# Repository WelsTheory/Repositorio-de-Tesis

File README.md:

# Diseño e implementación de un sistema de adquisición digital programable para señales ECG
Repositorio de la tesis "Diseño e implementación de un sistema de adquisición digital programable para señales ECG". Autor: William's Limonchi Sandoval
## Requisitos
Es necesario tener instalado los siguientes programas:
* [Matlab](https://www.mathworks.com/products/matlab.html) - La versión 2014 o superior
* [XC16](https://www.microchip.com/mplab/compilers) - El compilador XC16 para generar el programa del microcontrolador
* [Device Blocks for Simulink](https://www.microchip.com/forums/m878432.aspx) - Herramienta para trabajar con Microchip en Simulink
También es necesario tener la tarjeta de adquisición de la investigación para poder trabajar con el sistema. Los archivos de la tarjeta se encuentran en la carpeta Demo SAQD_ECG/Diseño Hardware_KiCad
### Carpetas del repositorio
* Carpeta de pruebas:
En esta carpeta se encuentran todos los ejemplos realizados antes de obtener el trabajo final
* Demo SAQD_ECG:
En esta carpeta se encuentra el programa principal de la tesis, desde el diseño de hardware de la investigación hasta el programa final con su interfaz gráfica.
* Ejemplos:
En esta carpeta se encuentran diferentes ejemplos que se han unido con el sistema. 
1) Downsamplin, para obtener otro tiempo de muestreos.
2) Filtros butterworth, para saber como trabajan los filtros butterworth con la investigación.
3) Filtros de 1er orden, son filtros sencillos de 1er orden para saber como trabaja la investigación
4) Sistema con tres filtros, es el programa principal con sólo 3 filtros.
5) Sistema con un único filtro, es el programa principal con un único filtro.
Estos programas son ejemplos para modificar el bloque Programable del programa principal. 
* Framework:
En esta carpeta se encuentra una copia del programa principal de la investigación, esto para poder modificar este programa sin necesidad de causar un error en el demo de la investigación.
## Contribución
Para contribuir con la investigación primero se debe hacer un fork al repositorio y seguidamente se puede enviar los cambios o modificaciones al correo: williams.limonchi.sandoval@gmail.com
## Version 
Esta investigación está en la versión 1.0.1 por lo que aún hay detalles que pulir y mejorar.
## Autor
William's Limonchi Sandoval [Twitter](http://twitter.com/welstheory)

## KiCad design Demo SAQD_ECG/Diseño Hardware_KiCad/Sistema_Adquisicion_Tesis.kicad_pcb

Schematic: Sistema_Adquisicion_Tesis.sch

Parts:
C1, C9: 100nF; C_Disc_D4.3mm_W1.9mm_P5.00mm
C2: 220uF; CP_Radial_D10.0mm_P5.00mm
C3, C4: 15pF; C_Disc_D3.0mm_W1.6mm_P2.50mm
C5, C6, C7, C8: 10uF; CP_Radial_D6.3mm_P2.50mm
D1, D2: 1N4148; D_DO-35_SOD27_P7.62mm_Horizontal
D3, D4: LED; LED_D5.0mm
J1: Barrel_Jack_Switch; Jack_Horizontal
J2: USB_SERIAL; PinHeader_1x04_P2.54mm_Vertical
J3: Signal_INA; PinHeader_1x03_P2.54mm_Vertical
J4: Offset; PinHeader_1x03_P2.54mm_Vertical
J5: Electrodos; Jack_3.5mm_Ledino_KB3SPRS_Horizontal
J6: DAC; PinHeader_1x03_P2.54mm_Vertical
J7: GND; PinHeader_1x02_P2.54mm_Vertical
J8: PORTA; PinSocket_1x05_P2.54mm_Vertical
J9: S_Fuente; PinHeader_1x03_P2.54mm_Vertical
J10: Pickit; PinHeader_1x05_P2.54mm_Vertical
J11: 3.3v; PinHeader_1x02_P2.54mm_Vertical
J12: PORTB; PinSocket_1x09_P2.54mm_Vertical
J13: V+; PinHeader_1x02_P2.54mm_Vertical
J14: V-; PinHeader_1x02_P2.54mm_Vertical
Q1: 2N3906; TO-92L_Inline_Wide
R1, R2: 1k; R_Axial_DIN0207_L6.3mm_D2.5mm_P7.62mm_Horizontal
R3, R4: 2k; R_Axial_DIN0207_L6.3mm_D2.5mm_P7.62mm_Horizontal
R5, R33, R35: 220; R_Axial_DIN0207_L6.3mm_D2.5mm_P7.62mm_Horizontal
R6, R7, R12: 5.6k; R_Axial_DIN0207_L6.3mm_D2.5mm_P7.62mm_Horizontal
R8, R19, R21, R23, R25, R27, R30, R36: 10k; R_Axial_DIN0207_L6.3mm_D2.5mm_P7.62mm_Horizontal
R9: 470; R_Axial_DIN0207_L6.3mm_D2.5mm_P7.62mm_Horizontal
R10, R11, R13, R14, R15, R16, R32: 1K; R_Axial_DIN0207_L6.3mm_D2.5mm_P7.62mm_Horizontal
R17, R18, R20, R22, R24, R26, R29, R31: 20k; R_Axial_DIN0207_L6.3mm_D2.5mm_P7.62mm_Horizontal
R28: 10K; R_Axial_DIN0207_L6.3mm_D2.5mm_P7.62mm_Horizontal
R34: 390; R_Axial_DIN0207_L6.3mm_D2.5mm_P7.62mm_Horizontal
SW1: RESET; SW_PUSH_6mm
U1: dsPIC33FJ128MC802-E_SP; DIP-28_W7.62mm
U2: INA128; DIP-8_W7.62mm
U3: L7805; TO-220-3_Vertical
U4, U7: TL082; DIP-8_W7.62mm
U5: LM317L_TO92; TO-220-3_Vertical
U6, U8: OP07; DIP-8_W7.62mm
U9: ADM660AN; DIP-8_W7.62mm
Y1: 10MHZ; Crystal_HC50_Vertical

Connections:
/3+: C9.1, J9.3, R35.2, U5.2
/3.3: J9.2, J11.1, J11.2, R36.2, U1.13, U1.28
/+IN: J5.T, J5.TN, R2.1
/-IN: J5.S, R1.1
/MCLR: J10.1, R36.1, SW1.1, U1.1
/OUT1: J3.2, R10.1
/OUT2: J4.3, U6.2, U6.6
/RA0: J4.2, J8.1, U1.2
/RA1: J8.2, R33.2, U1.3
/RA2: C3.1, J8.3, U1.9, Y1.1
/RA3: C4.1, J8.4, U1.10, Y1.2
/RA4: J8.5, U1.12
/RB0: J10.4, R18.1, U1.4
/RB1: J10.5, R20.1, U1.5
/RB2: R22.1, U1.6
/RB3: R24.1, U1.7
/RB4: R26.1, U1.11
/RB5: R29.1, U1.14
/RB6: R31.1, U1.15
/RB7: J12.1, U1.16
/RB8: J12.2, U1.17
/RB9: J12.3, U1.18
/RB12: J12.6, U1.23
/RB13: J12.7, U1.24
/RB14: J12.8, U1.25
/RB15: J12.9, U1.26
/RX: J2.2, J12.4, U1.21
/TC: J5.R, J5.RN, R28.1, U7.1
/TX: J2.3, J12.5, U1.22
/V+: C2.1, C8.1, D2.1, J13.1, J13.2, Q1.3, R9.1, R12.1, U2.7, U4.8 (V+), U5.3, U6.7, U7.8 (V+), U8.7, U9.8
/V-: C7.1, J14.1, J14.2, U2.4, U4.4 (V-), U6.4, U7.4 (V-), U8.4, U9.5
/Vp: J9.1, J10.2
/Vusb: J2.1, Q1.1, R8.1
/WCT: R3.1, R4.1, U8.3
GND: C1.2, C2.2, C3.2, C4.2, C5.1, C7.2, C8.2, C9.2, D1.1, D3.1, D4.1, J1.2, J1.3, J2.4, J3.1, J4.1, J6.1, J7.1, J7.2, J10.3, R6.2, R8.2, R15.2, R17.2, R34.1, SW1.2, U1.8, U1.19, U1.27, U2.5, U4.3 (+), U7.3 (+), U9.3
unnamed: C1.1, D2.2, R6.1, R7.1, U3.3
unnamed: C5.2, U1.20
unnamed: C6.1, U9.2
unnamed: C6.2, U9.4
unnamed: D1.2, U3.2
unnamed: D3.2, R9.2
unnamed: D4.2, R33.1
unnamed: J1.1, U3.1
unnamed: J3.3, U2.6
unnamed: J6.2, J6.3, R30.1, R31.2
unnamed: Q1.2, R7.2
unnamed: R1.2, U2.2
unnamed: R2.2, U2.3
unnamed: R3.2, R5.1, U2.1
unnamed: R4.2, R5.2, U2.8
unnamed: R10.2, R11.1, U4.2 (-)
unnamed: R11.2, R13.1, U4.1
unnamed: R12.2, R14.1, R15.1
unnamed: R13.2, R16.1, U4.6 (-)
unnamed: R14.2, U4.5 (+)
unnamed: R16.2, U4.7, U6.3
unnamed: R17.1, R18.2, R19.2
unnamed: R19.1, R20.2, R21.2
unnamed: R21.1, R22.2, R23.2
unnamed: R23.1, R24.2, R25.2
unnamed: R25.1, R26.2, R27.2
unnamed: R27.1, R29.2, R30.2
unnamed: R28.2, R32.1, U7.2 (-)
unnamed: R32.2, U8.2, U8.6
unnamed: R34.2, R35.1, U5.1

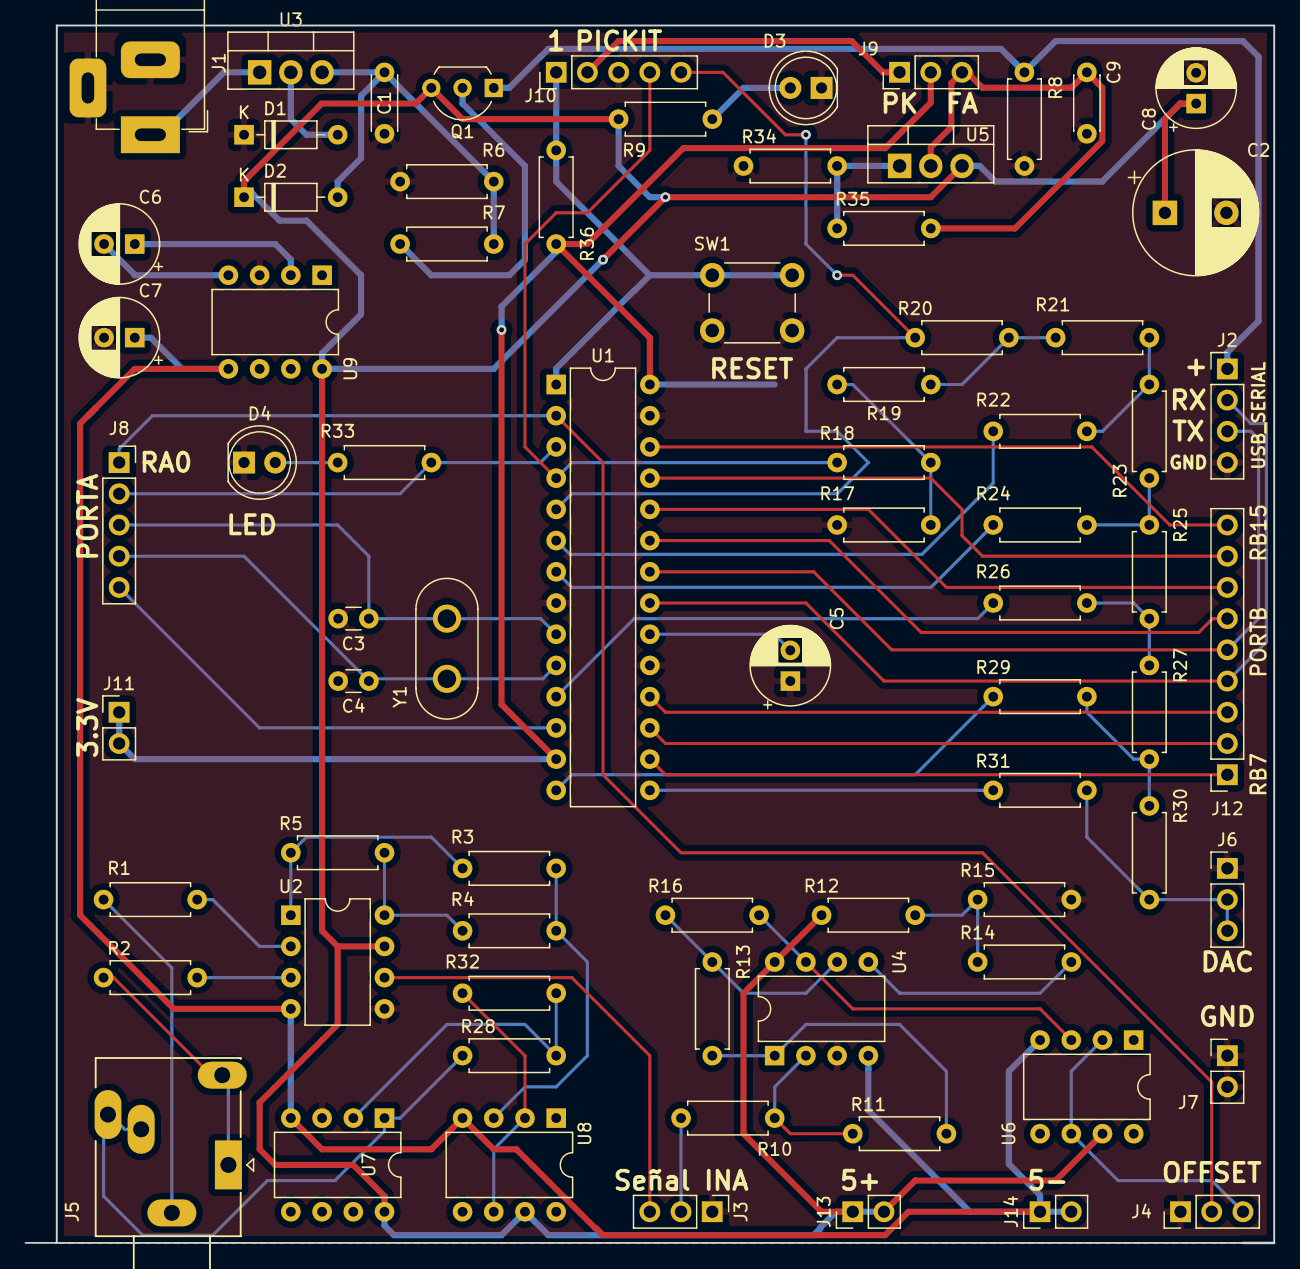
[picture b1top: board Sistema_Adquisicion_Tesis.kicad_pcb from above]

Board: 2 copper layers, 101.6 x 99.1 mm, 75 parts (0 on the bottom side), 65 nets.

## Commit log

2018-12-25 Carpeta de Pruebas y Plantilla de Readme
2018-12-25 Plantilla de Readme
2018-12-26 Versión 1.0 de la Tesis
2019-02-25 Repositorio de tesis 1.0.0.0.1
2019-02-26 Repositorio de Tesis, ordenado y actualizado
2019-02-26 Ejemplos y Framework del sistema
2019-02-26 Ejemplo de programa principal.x
2019-02-26 Descripción del repositorio
2019-02-26 Foto del sistema de investigación
2019-02-26 Guia del sistema
2019-07-12 Repositorio de Tesis
